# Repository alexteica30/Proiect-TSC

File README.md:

# Proiect InkTime - ESP32-C3 Smartwatch

Acest document contine specificatiile tehnice, Bill of Materials (BOM) si detaliile de design pentru proiectul InkTime.

## 1. Diagrama Bloc

# 2. Bill Of Materials (BOM)

Fisierul complet BOM poate fi gasit aici:

[bom.csv](Manufacturing/bom.csv)

# 3. Functionalitati Hardware

## Descrierea Detaliata a Functionalitatii Hardware

Proiectul InkTime este un smartwatch open-source proiectat in jurul unei arhitecturi compacte, cu accent pe integrare mecanica buna, consum redus de energie si posibilitatea de productie. Sistemul include un microcontroller cu conectivitate wireless, un subsistem de alimentare cu baterie reincarcabila, o interfata de afisare de tip e-paper, butoane pentru interactiunea utilizatorului si circuite de test si programare pentru dezvoltare si depanare.

Arhitectura hardware este organizata modular, astfel incat fiecare bloc functional sa poata fi rutat clar pe PCB si integrat in carcasa dispozitivului fara a compromite semnalul, alimentarea sau accesul la interfetele externe.

### 1. Unitatea centrala de procesare

* **nRF52840** reprezinta elementul central al sistemului si coordoneaza functionarea intregului dispozitiv.
* Acest circuit integreaza:
  * nucleul principal de procesare
  * comunicatia wireless Bluetooth Low Energy
  * controlul perifericelor externe
  * interfetele de programare si debug

### Rolul microcontrollerului

Microcontrollerul are urmatoarele responsabilitati principale:

* gestioneaza comunicatia cu display-ul
* citeste intrarile venite de la butoane
* controleaza actualizarile interfetei grafice
* permite transfer de date si depanare prin interfata USB si SWD
* coordoneaza starile de functionare active si low-power ale sistemului

Prin utilizarea unui SoC cu radio integrat, complexitatea placii este redusa, iar spatiul ocupat pe PCB este optimizat.

### 2. Managementul puterii

Subsistemul de alimentare a fost proiectat astfel incat dispozitivul sa poata functiona dintr-o baterie LiPo reincarcabila si sa poata fi incarcat prin USB-C.

Blocul de alimentare include:

* **port USB-C** pentru alimentare si incarcare
* **circuit de incarcare pentru bateria LiPo**
* **stabilizare si filtrare a tensiunilor de alimentare**
* **distributie separata a liniilor de alimentare**
* **test pad-uri pentru VBAT, 3V3, GND si alte semnale importante**

### Rolul subsistemului de alimentare

* permite alimentarea dispozitivului din USB
* permite incarcarea bateriei interne
* asigura tensiunea necesara pentru microcontroller si periferice
* reduce zgomotul electric prin condensatoare de decuplare plasate local
* permite masurare si depanare prin puncte de test dedicate

In layout-ul PCB se observa ca traseele de alimentare sunt rutate separat fata de semnalele de date, iar planurile de masa contribuie la stabilitate si la reducerea interferentelor.

### 3. Interfata de afisare

Dispozitivul foloseste un **display e-paper**, conectat printr-un conector dedicat de tip FPC.

### Avantajele acestei alegeri

* consum redus de energie
* vizibilitate buna in lumina ambientala
* pastrarea imaginii pe ecran fara consum continuu
* potrivit pentru un smartwatch orientat spre autonomie

### Rol hardware

* display-ul este controlat de microcontroller printr-o interfata digitala dedicata
* liniile suplimentare de control sunt folosite pentru selectie, reset, date/comenzi si semnal de stare
* conectorul FPC permite integrarea mecanica usoara in ansamblul final

### 4. Interfata utilizator

Interfata fizica cu utilizatorul este realizata printr-un set de **butoane tactile**, amplasate astfel incat sa se alinieze cu elementele mecanice ale carcasei.

### Rolul butoanelor

* navigare in meniu
* confirmare/selectie
* control al functiilor principale ale dispozitivului

Din punct de vedere hardware, aceste butoane sunt conectate la pini GPIO ai microcontrollerului si pot genera evenimente de tip intrerupere, ceea ce permite o functionare eficienta energetic.

### 5. Programare, debug si testare

Pentru dezvoltare si validare, placa include:

* interfata **SWD**
* puncte de test marcate pe silkscreen
* semnale expuse pentru:
  * SWDIO
  * SWCLK
  * RESET
  * GND
  * 3V3
  * VBAT
  * alte semnale utile in laborator

### Avantaje

* programare usoara a firmware-ului
* depanare rapida in timpul dezvoltarii
* verificare electrica a surselor si semnalelor
* suport bun pentru etapa de review si productie

Prezenta acestor puncte de test este importanta atat pentru debugging, cat si pentru verificarea functionala a placii.

### 6. Conectivitate wireless

Comunicatia wireless este asigurata de transceiverul radio integrat in nRF52840, impreuna cu antena dedicata de 2.4 GHz.

### Consideratii de proiectare RF

* antena este amplasata spre marginea placii
* zona din jurul antenei trebuie mentinuta cat mai libera de cupru si trasee
* retea de adaptare RF este utilizata pentru potrivirea impedantei
* planul de masa este controlat atent in zona radio

Aceste aspecte sunt esentiale pentru obtinerea unei performante bune a semnalului Bluetooth.

### 7. Protectie si componente pasive

Pentru functionare stabila si robusta, placa include:

* condensatoare de decuplare plasate cat mai aproape de pini de alimentare
* diode si componente de protectie pe liniile critice
* filtrare locala pentru reducerea zgomotului
* trasee scurte in jurul circuitelor importante
* via stitching intre planurile de masa

Aceste masuri contribuie la:

* stabilitatea alimentarii
* imunitate mai buna la zgomot
* comportament predictibil la incarcare si transmisie radio
* usurinta in validarea DRC/ERC

## Analiza Consumului de Energie si Autonomie

Proiectul InkTime este gandit ca un dispozitiv portabil, deci consumul de energie este un criteriu important. Estimarea autonomiei depinde de mai multi factori:

* timpul petrecut in sleep
* frecventa actualizarilor display-ului
* utilizarea comunicatiei Bluetooth
* activitatea butoanelor si a perifericelor
* eficienta regulatorului si pierderile pe alimentare

### 1. Componente cu impact major in consum

| Modul / Componenta | Standby / Sleep | Operare activa |
| :--- | :--- | :--- |
| **nRF52840** | foarte redus, in functie de modul low-power | consum mai mare in procesare si BLE |
| **Display e-paper** | aproape zero pentru imagine statica | consum doar la refresh |
| **Circuite de alimentare** | consum propriu redus | depinde de sarcina |
| **Butoane / GPIO** | neglijabil | impulsuri scurte |

### 2. Scenariu de utilizare tipic

Un scenariu realist pentru InkTime presupune:

* majoritatea timpului in sleep
* trezire periodica pentru actualizare
* refresh rar al display-ului
* utilizare ocazionala a Bluetooth
* interactiuni scurte prin butoane

In acest mod de functionare, consumul mediu poate ramane redus, iar autonomia creste semnificativ fata de un dispozitiv cu ecran activ permanent.

### 3. Estimare autonomie

Autonomia depinde direct de:

* capacitatea bateriei LiPo folosite
* consumul mediu rezultat din duty cycle
* frecventa comunicarilor wireless
* numarul de refresh-uri ale display-ului

Formula generala utilizata este:

`Autonomie (ore) = Capacitate baterie (mAh) / Consum mediu (mA)`

Deoarece autonomia exacta depinde de firmware si de scenariul real de utilizare, aceasta trebuie validata experimental pe prototipul fizic.

# 4. Alocare pini si interfete hardware

## 1. Alimentare

### Semnale principale

* VBAT
* 3V3
* GND
* VBUS

### Rol

* **VBAT** alimenteaza sistemul din bateria LiPo
* **VBUS** vine din portul USB-C
* **3V3** alimenteaza logica digitala si microcontrollerul
* **GND** reprezinta referinta comuna a intregului sistem

### Observatii

* semnalele de alimentare sunt scoase si in test pad-uri
* traseele de alimentare sunt rutate mai lat decat semnalele de date
* condensatoarele de decuplare sunt plasate aproape de componentele active

## 2. Interfata RF

### Blocuri implicate

* iesirea RF a microcontrollerului
* reteaua de adaptare
* antena de 2.4 GHz

### Rol

* transmite si receptioneaza semnalul Bluetooth
* asigura conectivitate wireless pentru smartwatch

### Observatii de proiectare

* antena este pozitionata la marginea PCB-ului
* sub antena trebuie evitata turnarea de cupru
* traseul RF trebuie pastrat cat mai scurt si controlat

## 3. Oscilatoare

Microcontrollerul foloseste surse de ceas necesare functionarii corecte a sistemului.

### Rol

* stabilitate pentru functionarea nucleului principal
* precizie pentru comunicatia radio
* suport pentru modurile low-power si temporizare

### Observatii

* cristalele si componentele asociate trebuie plasate aproape de pini
* traseele aferente trebuie sa fie scurte si simetrice

## 4. Programare si debug

### Semnale principale

* SWDIO
* SWCLK
* RESET
* GND

### Rol

* programarea firmware-ului
* depanare in timpul dezvoltarii
* testare in laborator

### Implementare pe placa

* semnalele sunt disponibile prin interfata de programare
* exista test pad-uri etichetate clar in silkscreen

## 5. Interfata USB

### Semnale principale

* VBUS
* D+
* D-
* GND

### Rol

* alimentare a dispozitivului
* incarcare a bateriei
* eventuala comunicatie de date, in functie de implementarea firmware

### Protectii

* liniile USB includ protectie ESD
* conectorul USB-C este integrat mecanic in partea superioara a placii

## 6. Interfata display

### Semnale utilizate

In functie de schema, display-ul foloseste o combinatie de semnale de date si control, tipic:

* MOSI
* SCK
* CS
* DC
* RST
* BUSY

### Rol

* transmiterea datelor catre display
* controlul comenzilor de refresh si reset
* citirea semnalului de stare al display-ului

### Implementare

* display-ul este conectat prin conector FPC
* semnalele sunt rutate compact pentru a minimiza zgomotul si interferentele

## 7. GPIO si butoane

### Semnale implicate

* intrari digitale pentru butoane
* eventual semnale de intrerupere

### Rol

* navigare in interfata
* comenzi utilizator
* activare a anumitor functii ale sistemului

### Observatii

* butoanele sunt plasate pentru alinierea cu carcasa
* pot fi utilizate in mod polling sau interrupt-driven

## 8. Test pad-uri si semnale de laborator

Placa include mai multe puncte de test utile pentru validare si depanare, cum ar fi:

* TP_GND
* TP_3V3
* TP_VBAT
* TP_RESET
* TP_SWDIO
* TP_SWCLK
* alte semnale utile din schema

### Avantaje

* diagnostic rapid
* verificarea surselor
* acces usor la semnale fara a modifica traseele principale

## 9. Integrare mecanica

Designul PCB-ului a fost realizat astfel incat:

* sa respecte forma mecanica a carcasei
* sa permita accesul la portul USB-C
* sa alinieze butoanele cu elementele externe
* sa permita montarea display-ului si bateriei in ansamblul final

Forma placii, pozitionarea conectorilor si gruparea functionala a componentelor urmaresc atat cerintele electrice, cat si constrangerile mecanice impuse de produs.

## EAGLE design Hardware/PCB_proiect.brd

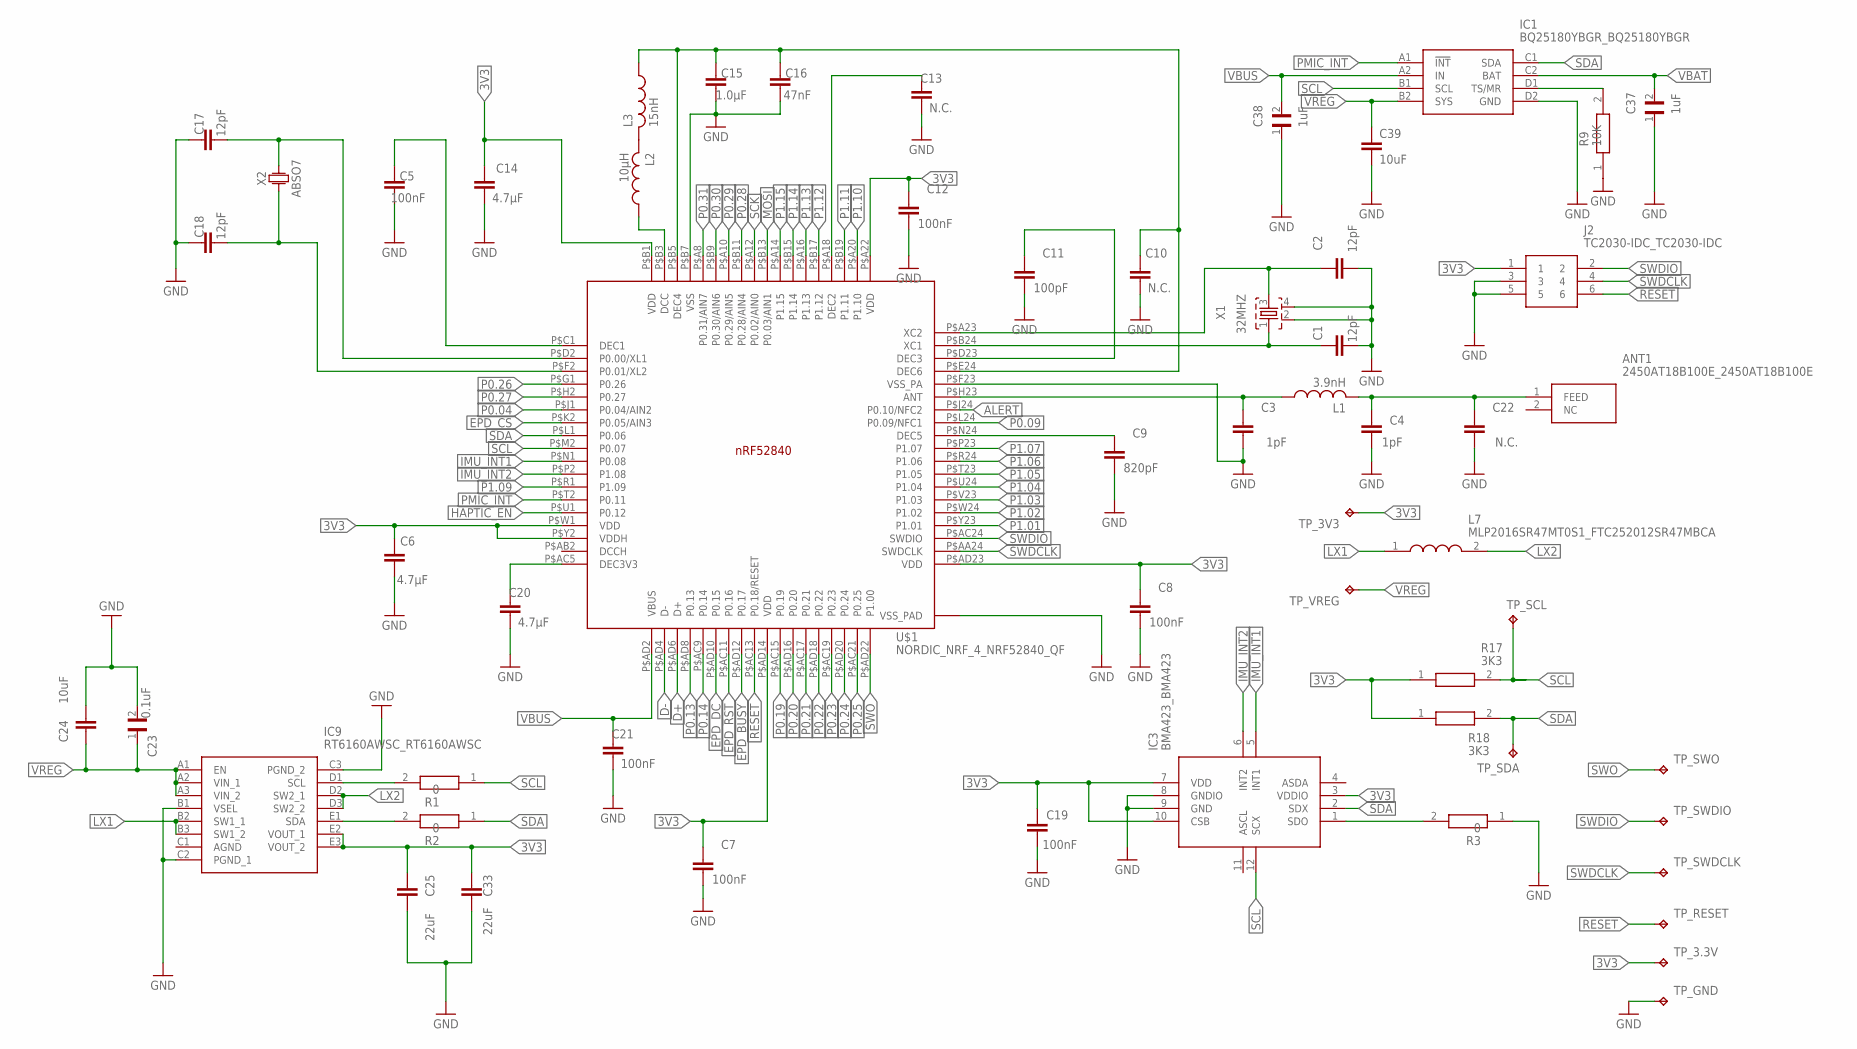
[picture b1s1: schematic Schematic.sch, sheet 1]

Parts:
ANT1: 2450AT18B100E_2450AT18B100E; 2450AT18B100E_ANTC3216X140N
C1, C2, C17, C18: 12pF; NORDIC_NRF_3_RESC0201_L
C3, C4: 1pF; NORDIC_NRF_3_RESC0201_L
C5, C7, C8, C12, C19, C21: 100nF; NORDIC_NRF_3_RESC0201_L
C6, C14, C20: 4.7µF; NORDIC_NRF_3_RESC0201_L
C9: 820pF; NORDIC_NRF_3_RESC0201_L
C10, C13, C22: N.C.; NORDIC_NRF_3_RESC0201_L
C11: 100pF; NORDIC_NRF_3_RESC0201_L
C15: 1.0µF; NORDIC_NRF_3_RESC0201_L
C16: 47nF; NORDIC_NRF_3_RESC0201_L
C23: 0.1uF; GRM011R60J152KE01L_2_CAPC0201X13N
C24, C39: 10uF; NORDIC_NRF_3_RESC0201_L
C25, C33: 22uF; NORDIC_NRF_3_RESC0201_L
C37, C38: 1uF; GRM011R60J152KE01L_2_CAPC0201X13N
IC1: BQ25180YBGR_BQ25180YBGR; BQ25180YBGR_BGA8C40P2X4_100X155X50
IC3: BMA423_BMA423
IC9: RT6160AWSC_RT6160AWSC; RT6160AWSC_BGA15C40P3X5_140X230X60
J2: TC2030-IDC_TC2030-IDC; TC2030-IDC_TC2030IDC
L1: 3.9nH; NORDIC_NRF_2_RESC0402_L
L2: 10µH; NORDIC_NRF_2_RESC0402_L
L3: 15nH; NORDIC_NRF_2_RESC0402_L
L7: MLP2016SR47MT0S1_FTC252012SR47MBCA; MLP2016SR47MT0S1_INDC2016X100N
R1, R2, R3: 0; ERA-1AEB3401C_0201
R9: 10K; ERA-1AEB3401C_0201
R17, R18: 3K3; ERA-1AEB3401C_0201
TP_3.3V, TP_3V3: HECTOR_WATCH_1_TPTP20R; HECTOR_WATCH_1_TP20R
TP_GND: HECTOR_WATCH_1_TPTP20R; HECTOR_WATCH_1_TP20R
TP_RESET: HECTOR_WATCH_1_TPTP20R; HECTOR_WATCH_1_TP20R
TP_SCL: HECTOR_WATCH_1_TPTP20R; HECTOR_WATCH_1_TP20R
TP_SDA: HECTOR_WATCH_1_TPTP20R; HECTOR_WATCH_1_TP20R
TP_SWDCLK: HECTOR_WATCH_1_TPTP20R; HECTOR_WATCH_1_TP20R
TP_SWDIO: HECTOR_WATCH_1_TPTP20R; HECTOR_WATCH_1_TP20R
TP_SWO: HECTOR_WATCH_1_TPTP20R; HECTOR_WATCH_1_TP20R
TP_VREG: HECTOR_WATCH_1_TPTP20R; HECTOR_WATCH_1_TP20R
U$1: NORDIC_NRF_4_NRF52840_QF; NORDIC_NRF_4_AQFN50P700X700X85_HS-74N
X1: 32MHZ; NORDIC_NRF_BT-XTAL_2016_N
X2: ABSO7; XTAL_ABS07-32.768KHZ-T

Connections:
3V3: C6.1, C7.2, C8.2, C12.2, C14.1, C19.2, C25.2, C33.1, IC3.3 (VDDIO), IC3.7 (VDD), IC3.10 (CSB), IC9.E2 (VOUT_1), IC9.E3 (VOUT_2), J2.1, R17.1, R18.1, TP_3.3V.TP, TP_3V3.TP, U$1.P$A22 (VDD), U$1.P$AD14 (VDD), U$1.P$AD23 (VDD), U$1.P$B1 (VDD), U$1.P$W1 (VDD), U$1.P$Y2 (VDDH); also elsewhere on the board
ALERT: U$1.P$J24 (P0.10/NFC2); also elsewhere on the board
D+: U$1.P$AD6 (D+); also elsewhere on the board
D-: U$1.P$AD4 (D-); also elsewhere on the board
EPD_BUSY: U$1.P$AD12 (P0.17); also elsewhere on the board
EPD_CS: U$1.P$K2 (P0.05/AIN3); also elsewhere on the board
EPD_DC: U$1.P$AD10 (P0.15); also elsewhere on the board
EPD_RST: U$1.P$AC11 (P0.16); also elsewhere on the board
GND: C1.1, C2.1, C3.1, C4.1, C5.1, C6.2, C7.1, C8.1, C9.1, C10.1, C11.1, C12.1, C13.2, C14.2, C15.1, C16.1, C17.2, C18.2, C19.1, C20.2, C21.2, C22.1, C23.2, C24.1, C25.1, C33.2, C37.1, C38.1, C39.2, IC1.D2 (GND), IC3.8 (GNDIO), IC3.9 (GND), IC9.B1 (VSEL), IC9.C2 (PGND_1), IC9.C3 (PGND_2), J2.3, J2.5, R3.1, R9.1, TP_GND.TP, U$1.P$74 (VSS_PAD), U$1.P$75 (VSS_PAD), U$1.P$76 (VSS_PAD), U$1.P$77 (VSS_PAD), U$1.P$78 (VSS_PAD), U$1.P$79 (VSS_PAD), U$1.P$80 (VSS_PAD), U$1.P$81 (VSS_PAD), U$1.P$82 (VSS_PAD), U$1.P$83 (VSS_PAD), U$1.P$84 (VSS_PAD), U$1.P$85 (VSS_PAD), U$1.P$86 (VSS_PAD), U$1.P$87 (VSS_PAD), U$1.P$88 (VSS_PAD), U$1.P$89 (VSS_PAD), U$1.P$90 (VSS_PAD), U$1.P$B7 (VSS), U$1.P$F23 (VSS_PA), X1.2, X1.4; also elsewhere on the board
HAPTIC_EN: U$1.P$U1 (P0.12); also elsewhere on the board
IMU_INT1: IC3.5 (INT1), U$1.P$N1 (P0.08)
IMU_INT2: IC3.6 (INT2), U$1.P$P2 (P1.08)
LX1: IC9.B2 (SW1_1), IC9.B3 (SW1_2), L7.1
LX2: IC9.D2 (SW2_1), IC9.D3 (SW2_2), L7.2
MOSI: U$1.P$B13 (P0.03/AIN1); also elsewhere on the board
unnamed: IC1.D1 (TS/MR), R9.2
unnamed: IC9.D1 (SCL), R1.2
unnamed: IC9.E1 (SDA), R2.2
unnamed: IC3.1 (SDO), R3.2
unnamed: C20.1, U$1.P$AC5 (DEC3V3)
unnamed: C9.2, U$1.P$N24 (DEC5)
unnamed: C3.2, L1.1, U$1.P$H23 (ANT)
unnamed: C11.2, U$1.P$D23 (DEC3)
unnamed: L2.1, U$1.P$B3 (DCC)
unnamed: C2.2, U$1.P$A23 (XC2), X1.3
unnamed: C1.2, U$1.P$B24 (XC1), X1.1
unnamed: C13.1, U$1.P$A18 (DEC2)
unnamed: C10.2, C15.2, C16.2, L3.1, U$1.P$B5 (DEC4), U$1.P$E24 (DEC6)
unnamed: L2.2, L3.2
unnamed: C5.2, U$1.P$C1 (DEC1)
unnamed: C17.1, U$1.P$D2 (P0.00/XL1), X2.2
unnamed: C18.1, U$1.P$F2 (P0.01/XL2), X2.1
P0.04: U$1.P$J1 (P0.04/AIN2)
P0.09: U$1.P$L24 (P0.09/NFC1)
P0.13: U$1.P$AD8 (P0.13); also elsewhere on the board
P0.14: U$1.P$AC9 (P0.14); also elsewhere on the board
P0.19: U$1.P$AC15 (P0.19)
P0.20: U$1.P$AD16 (P0.20)
P0.21: U$1.P$AC17 (P0.21)
P0.22: U$1.P$AD18 (P0.22)
P0.23: U$1.P$AC19 (P0.23)
P0.24: U$1.P$AD20 (P0.24)
P0.25: U$1.P$AC21 (P0.25)
P0.26: U$1.P$G1 (P0.26)
P0.27: U$1.P$H2 (P0.27)
P0.28: U$1.P$B11 (P0.28/AIN4)
P0.29: U$1.P$A10 (P0.29/AIN5)
P0.30: U$1.P$B9 (P0.30/AIN6)
P0.31: U$1.P$A8 (P0.31/AIN7)
P1.01: U$1.P$Y23 (P1.01); also elsewhere on the board
P1.02: U$1.P$W24 (P1.02); also elsewhere on the board
P1.03: U$1.P$V23 (P1.03)
P1.04: U$1.P$U24 (P1.04)
P1.05: U$1.P$T23 (P1.05)
P1.06: U$1.P$R24 (P1.06)
P1.07: U$1.P$P23 (P1.07)
P1.09: U$1.P$R1 (P1.09)
P1.10: U$1.P$A20 (P1.10)
P1.11: U$1.P$B19 (P1.11)
P1.12: U$1.P$B17 (P1.12)
P1.13: U$1.P$A16 (P1.13)
P1.14: U$1.P$B15 (P1.14)
P1.15: U$1.P$A14 (P1.15)
PMIC_INT: IC1.A1 (!INT), U$1.P$T2 (P0.11)
RESET: J2.6, TP_RESET.TP, U$1.P$AC13 (P0.18/RESET)
RF: ANT1.1 (FEED), C4.2, C22.2, L1.2
SCK: U$1.P$A12 (P0.02/AIN0); also elsewhere on the board
SCL: IC1.B1 (SCL), IC3.12 (SCX), R1.1, R17.2, TP_SCL.TP, U$1.P$M2 (P0.07); also elsewhere on the board
SDA: IC1.C1 (SDA), IC3.2 (SDX), R2.1, R18.2, TP_SDA.TP, U$1.P$L1 (P0.06); also elsewhere on the board
SWDCLK: J2.4, TP_SWDCLK.TP, U$1.P$AA24 (SWDCLK)
SWDIO: J2.2, TP_SWDIO.TP, U$1.P$AC24 (SWDIO)
SWO: TP_SWO.TP, U$1.P$AD22 (P1.00)
VBAT: C37.2, IC1.C2 (BAT); also elsewhere on the board
VBUS: C21.1, C38.2, IC1.A2 (IN), U$1.P$AD2 (VBUS); also elsewhere on the board
VREG: C23.1, C24.2, C39.1, IC1.B2 (SYS), IC9.A1 (EN), IC9.A2 (VIN_1), IC9.A3 (VIN_2), TP_VREG.TP

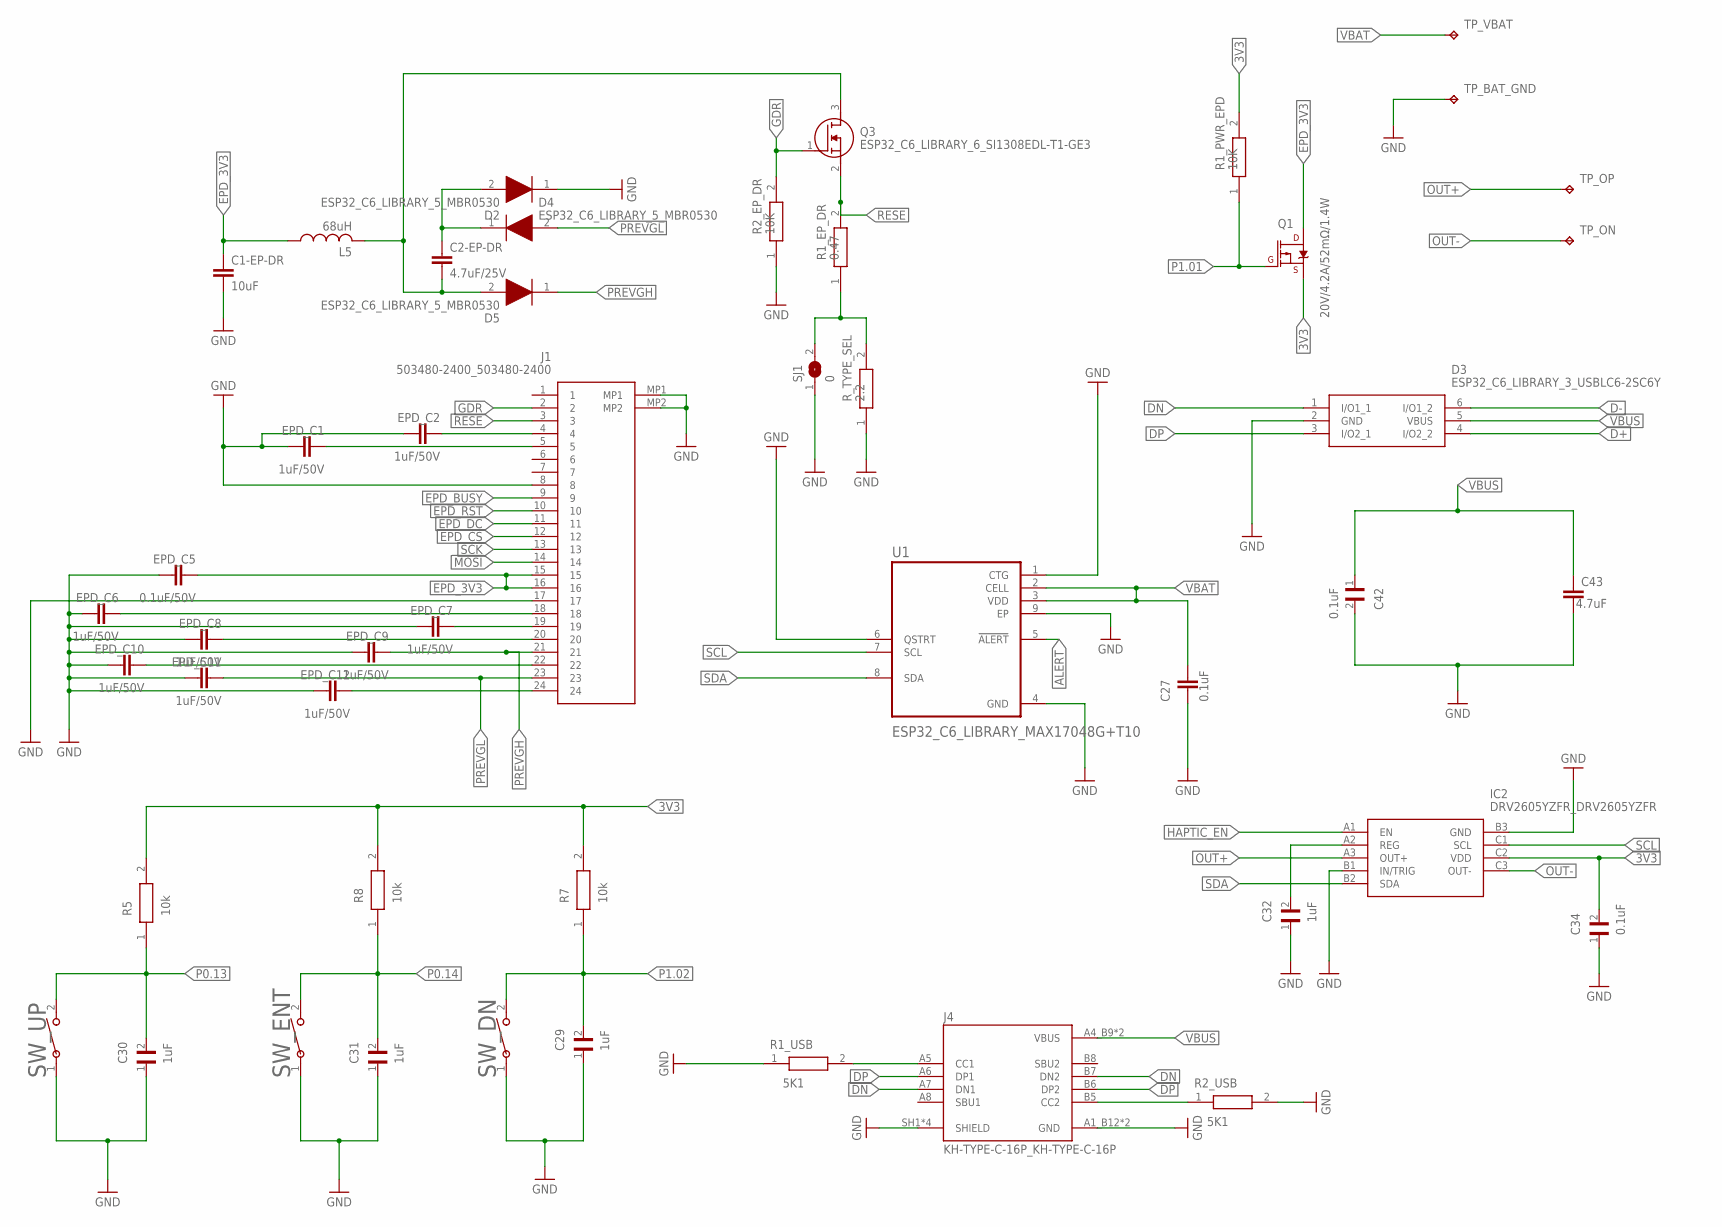
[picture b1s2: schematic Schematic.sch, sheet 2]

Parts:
C1-EP-DR: 10uF; NORDIC_NRF_3_RESC0201_L
C2-EP-DR: 4.7uF/25V; NORDIC_NRF_3_RESC0201_L
C27: 0.1uF; NORDIC_NRF_3_RESC0201_L
C29, C30, C31, C32: 1uF; GRM011R60J152KE01L_1_0201
C34, C42: 0.1uF; GRM011R60J152KE01L_1_0201
C43: 4.7uF; NORDIC_NRF_3_RESC0201_L
D2, D4, D5: ESP32_C6_LIBRARY_5_MBR0530; ESP32_C6_LIBRARY_5_SOD3716X135N
D3: ESP32_C6_LIBRARY_3_USBLC6-2SC6Y; ESP32_C6_LIBRARY_3_SOT95P280X145-6N
EPD_C1, EPD_C2, EPD_C6, EPD_C7, EPD_C8, EPD_C9, EPD_C10, EPD_C11, EPD_C12: 1uF/50V; NORDIC_NRF_3_RESC0201_L
EPD_C5: 0.1uF/50V; NORDIC_NRF_3_RESC0201_L
IC2: DRV2605YZFR_DRV2605YZFR; DRV2605YZFR_BGA9C50P3X3_144X144X62
J1: 503480-2400_503480-2400; 503480-2400_5034802400
J4: KH-TYPE-C-16P_KH-TYPE-C-16P; KH-TYPE-C-16P_KINGHELM_KH-TYPE-C-16P
L5: 68uH; NORDIC_NRF_2_RESC0402_L
Q1: 20V/4.2A/52mΩ/1.4W; ESP32_C6_LIBRARY_4_ESP32_C6_LIBRARY_4_ESP32_C6_LIBRARY_4_ES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
Q3: ESP32_C6_LIBRARY_6_SI1308EDL-T1-GE3; ESP32_C6_LIBRARY_6_SOT65P210X110-3N
R1_EP_DR: 0.47; CPF0201D7K68C1_0201
R1_PWR_EPD, R2_EP_DR: 10K; CPF0201D7K68C1_0201
R1_USB, R2_USB: 5K1; CPF0201D7K68C1_0201
R5, R7, R8: 10k; CPF0201D7K68C1_0201
R_TYPE_SEL: 2.2; CPF0201D7K68C1_0201
SJ1: 0; ESP32_C6_LIBRARY_7_JUMPER_SJ
SW_DN: 2025-10-22_07-23-44_LIBRARY_EVP-AKE31ASW_EVP-AKE3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; 2025-10-22_07-23-44_LIBRARY_SW_EVP-AKE31A_PAN
SW_ENT: 2025-10-22_07-23-44_LIBRARY_EVP-AKE31ASW_EVP-AKE3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; 2025-10-22_07-23-44_LIBRARY_SW_EVP-AKE31A_PAN
SW_UP: 2025-10-22_07-23-44_LIBRARY_EVP-AKE31ASW_EVP-AKE3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; 2025-10-22_07-23-44_LIBRARY_SW_EVP-AKE31A_PAN
TP_BAT_GND: HECTOR_WATCH_1_TPTP20R; HECTOR_WATCH_1_TP20R
TP_ON: HECTOR_WATCH_1_TPTP20R; HECTOR_WATCH_1_TP20R
TP_OP: HECTOR_WATCH_1_TPTP20R; HECTOR_WATCH_1_TP20R
TP_VBAT: HECTOR_WATCH_1_TPTP20R; HECTOR_WATCH_1_TP20R
U1: ESP32_C6_LIBRARY_MAX17048G+T10; ESP32_C6_LIBRARY_SON50P200X200X80-9N

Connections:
3V3: C34.2, IC2.C2 (VDD), Q1.2 (S), R1_PWR_EPD.2, R5.2, R7.2, R8.2; also elsewhere on the board
ALERT: U1.5 (!ALERT); also elsewhere on the board
D+: D3.4 (I/O2_2); also elsewhere on the board
D-: D3.6 (I/O1_2); also elsewhere on the board
DN: D3.1 (I/O1_1), J4.A7 (DN1), J4.B7 (DN2)
DP: D3.3 (I/O2_1), J4.A6 (DP1), J4.B6 (DP2)
EPD_BUSY: J1.9; also elsewhere on the board
EPD_CS: J1.12; also elsewhere on the board
EPD_DC: J1.11; also elsewhere on the board
EPD_RST: J1.10; also elsewhere on the board
GDR: J1.2, Q3.1 (G), R2_EP_DR.2
GND: C1-EP-DR.2, C27.2, C29.1, C30.1, C31.1, C32.1, C34.1, C42.2, C43.2, D2.1 (K), D3.2 (GND), EPD_C1.1, EPD_C2.1, EPD_C5.1, EPD_C6.1, EPD_C7.1, EPD_C8.1, EPD_C9.1, EPD_C10.1, EPD_C11.1, EPD_C12.1, IC2.B1 (IN/TRIG), IC2.B3 (GND), J1.8, J1.17, J1.MP1, J1.MP2, J4.A1_B12 (GND), J4.A12_B1 (GND), J4.SH1 (SHIELD), J4.SH2 (SHIELD), J4.SH3 (SHIELD), J4.SH4 (SHIELD), R1_USB.1, R2_EP_DR.1, R2_USB.2, R_TYPE_SEL.1, SJ1.1, SW_DN.1, SW_ENT.1, SW_UP.1, TP_BAT_GND.TP, U1.1 (CTG), U1.4 (GND), U1.6 (QSTRT), U1.9 (EP); also elsewhere on the board
HAPTIC_EN: IC2.A1 (EN); also elsewhere on the board
MOSI: J1.14; also elsewhere on the board
unnamed: C2-EP-DR.1, D2.2 (A), D4.1 (K)
unnamed: R1_EP_DR.1, R_TYPE_SEL.2, SJ1.2
unnamed: EPD_C2.2, J1.4
unnamed: EPD_C6.2, J1.18
unnamed: EPD_C1.2, J1.5
unnamed: EPD_C7.2, J1.19
unnamed: EPD_C8.2, J1.20
unnamed: J4.A5 (CC1), R1_USB.2
unnamed: EPD_C10.2, J1.22
unnamed: J4.B5 (CC2), R2_USB.1
unnamed: EPD_C12.2, J1.24
unnamed: C32.2, IC2.A2 (REG)
OUT+: IC2.A3 (OUT+), TP_OP.TP
OUT-: IC2.C3 (OUT-), TP_ON.TP
P0.13: C30.2, R5.1, SW_UP.2; also elsewhere on the board
P0.14: C31.2, R8.1, SW_ENT.2; also elsewhere on the board
P1.01: Q1.1 (G), R1_PWR_EPD.1; also elsewhere on the board
P1.02: C29.2, R7.1, SW_DN.2; also elsewhere on the board
PREVGH: D5.1 (K), EPD_C9.2, J1.21
PREVGL: D4.2 (A), EPD_C11.2, J1.23
RESE: J1.3, Q3.2 (S), R1_EP_DR.2
SCK: J1.13; also elsewhere on the board
SCL: IC2.C1 (SCL), U1.7 (SCL); also elsewhere on the board
SDA: IC2.B2 (SDA), U1.8 (SDA); also elsewhere on the board
VBAT: C27.1, TP_VBAT.TP, U1.2 (CELL), U1.3 (VDD); also elsewhere on the board
VBUS: C42.1, C43.1, D3.5 (VBUS), J4.A4_B9 (VBUS), J4.A9_B4 (VBUS); also elsewhere on the board

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
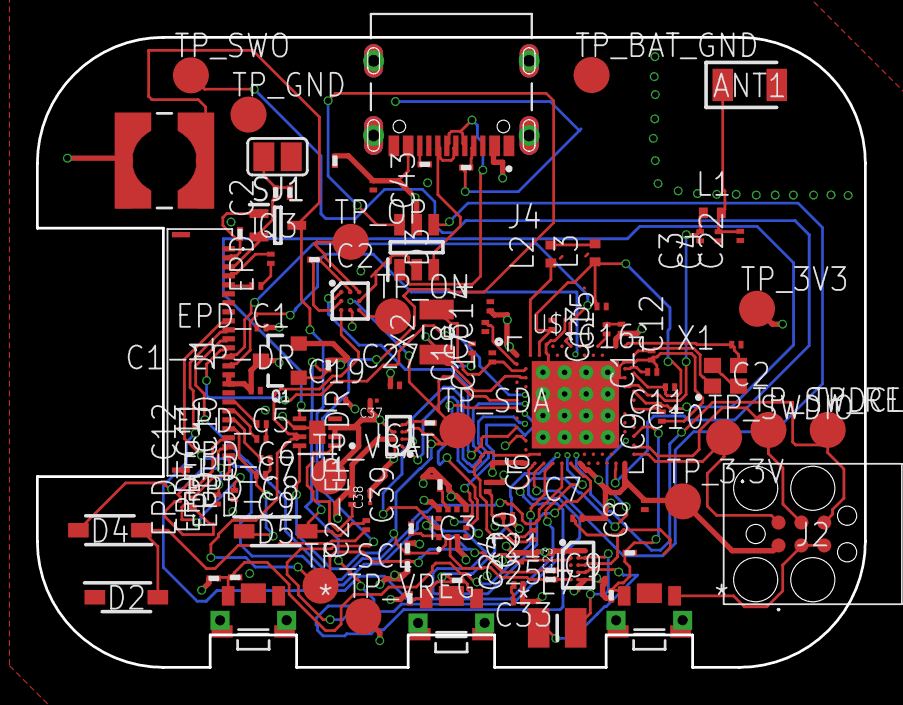
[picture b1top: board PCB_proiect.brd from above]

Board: 2 copper layers, 46.0 x 35.0 mm, 105 parts (0 on the bottom side), 70 nets.

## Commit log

2026-04-10 Create Hardware
2026-04-10 Rename PCB_proiect.brd to Hardware/PCB_project.brd
2026-04-10 Rename Schematic.sch to Hardware/Schematic.sch
2026-04-10 Rename PCB_proiect.brd to Hardware/PCB_proiect.brd
2026-04-15 Add Apache License 2.0
    Added the Apache License 2.0 to the project.
2026-04-16 Rename gerbers.zip to Manufacturing/gerbers.zip
2026-04-16 Rename Schematic.pdf to Hardware/Schematic.pdf
2026-04-19 Rename ceas_exploded.png to Images/ceas_exploded.png
2026-04-19 Rename ceas_exploded2.png to Images/ceas_exploded2.png
2026-04-19 Rename forma_finala.png to Images/forma_finala.png
2026-04-19 Rename mufa_usb.png to Images/mufa_usb.png
2026-04-19 Rename pcb_3d_bottom.png to Images/pcb_3d_bottom.png
2026-04-19 Rename pcb_3d_top.png to Images/pcb_3d_top.png
2026-04-19 Rename pcb_cu_rutare.png to Images/pcb_cu_rutare.png
2026-04-19 Rename Project_final_asm.f3z to Mechanical/Project_final_asm.f3z
2026-04-19 Rename Exploded_view.stp to Mechanical/Exploded_view.stp
2026-04-22 Rename diagrama.png to Diagrama.png

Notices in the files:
parts and their libraries:
COPYRIGHT: Copyright (C) 2025 Ultra Librarian. All rights reserved.
COPYRIGHT: Copyright (C) 2024 Ultra Librarian. All rights reserved.
